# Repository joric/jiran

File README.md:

# Jiran Keyboard

Jiran keyboard - is a ergo split keyboard.

This is archived copy. Actual version is at https://github.com/Ladniy/jiran-keyboard

## Downloads

* [TheCoolerJiran_Gerbers.zip](https://github.com/joric/jiran/raw/master/Jiran/Gerbers/TheCoolerJiran_Gerbers.zip)

## Pictures

## References

* https://github.com/Ladniy/Jiran

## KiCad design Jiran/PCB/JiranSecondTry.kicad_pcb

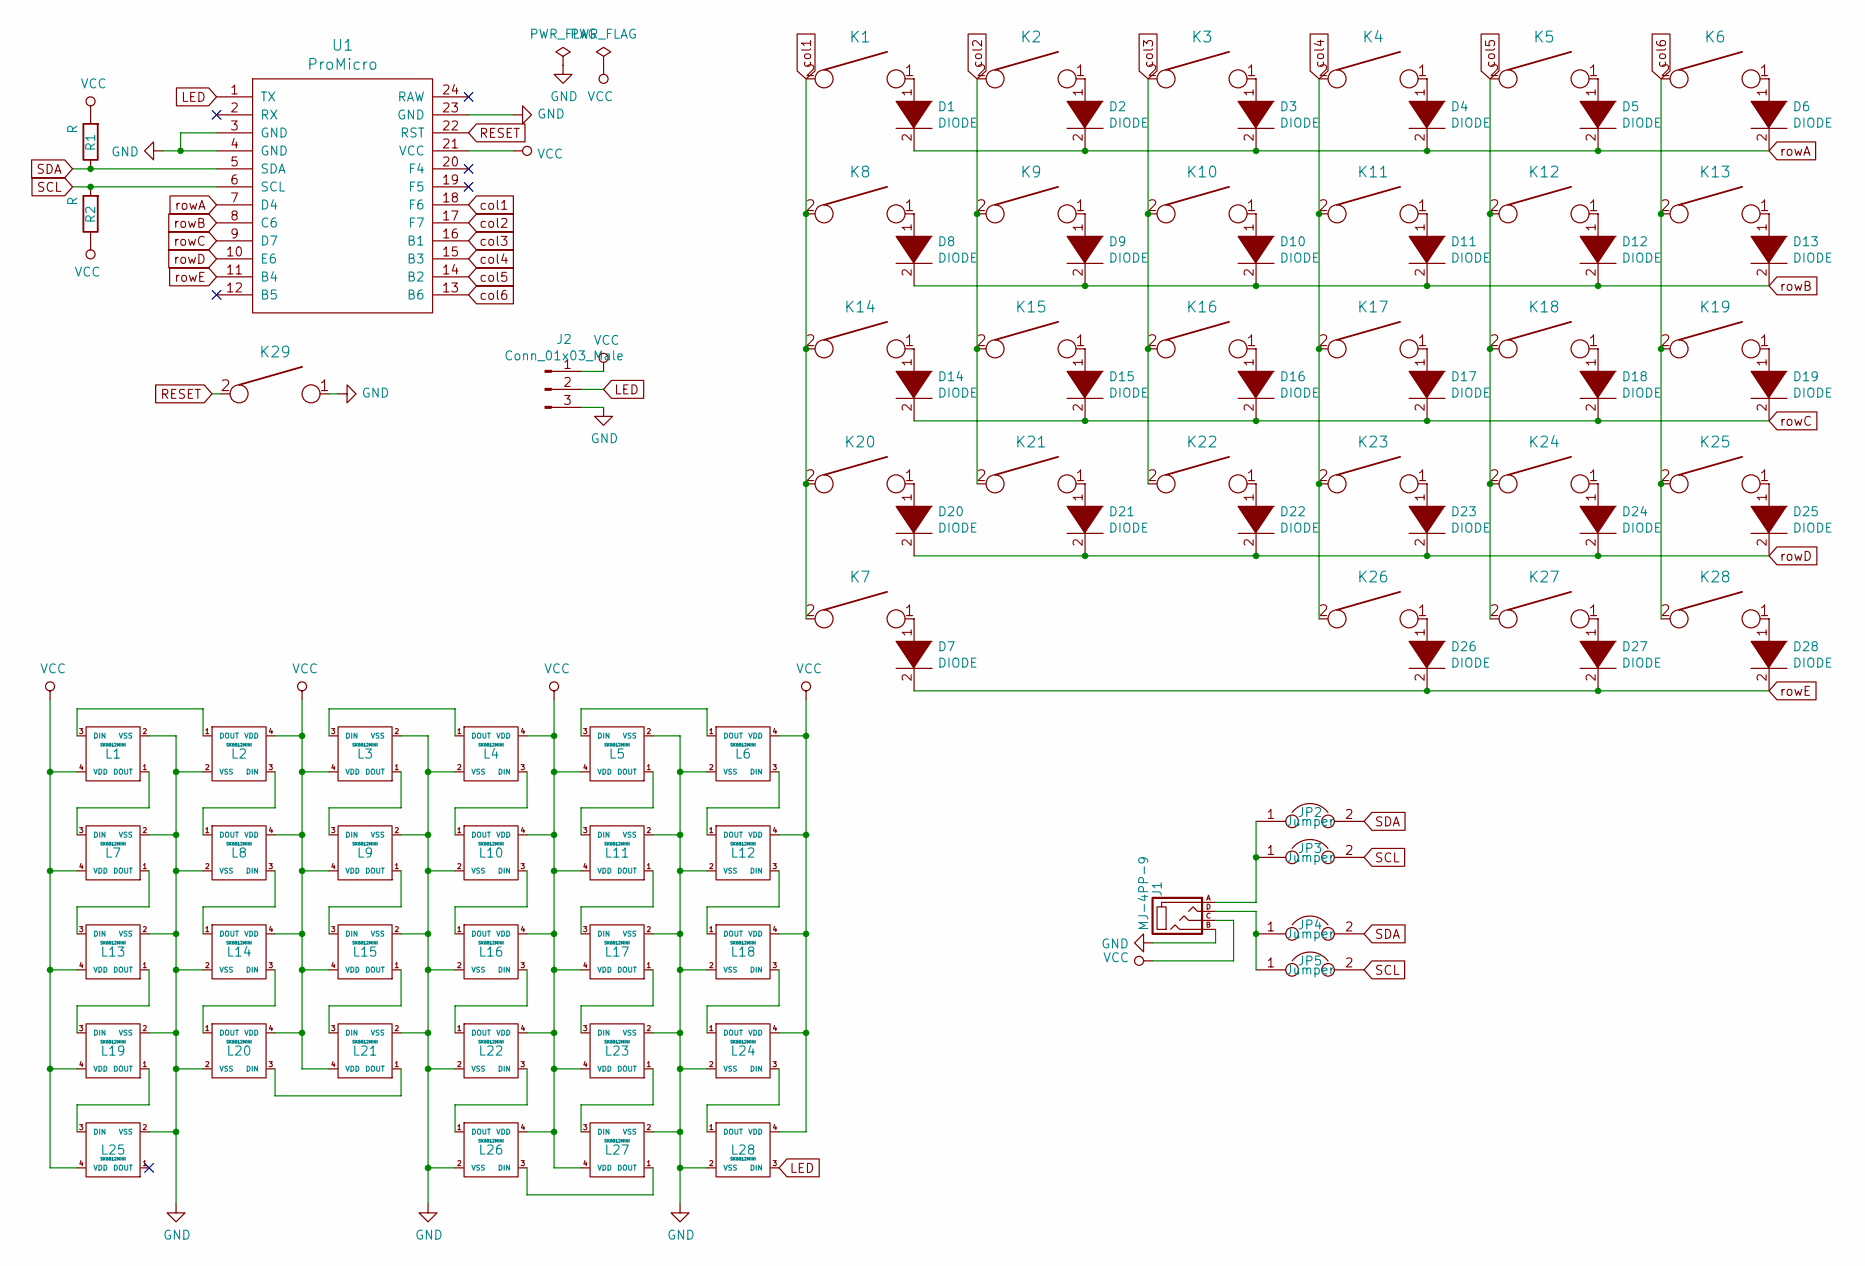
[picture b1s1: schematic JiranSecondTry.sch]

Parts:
D1, D2, D3, D4, D5, D6, D7, D8, D9, D10, D11, D12, D13, D14, D15, D16, D17, D18, D19, D20, D21, D22, D23, D24, D25, D26, D27, D28: DIODE; Diode-dual
J1: MJ-4PP-9; MJ-4PP-9_Dual
J2: Conn_01x03_Male; 3_Pin_Jumper
JP2, JP3, JP4, JP5: Jumper
K1, K2, K3, K4, K5, K6, K7, K8, K9, K10, K11, K12, K13, K14, K15, K16, K17, K18, K19, K20, K21, K22, K23, K24, K25, K26, K27, K28: KEYSW; MX_ALPS_PG1350_noLed
K29: KEYSW; ResetSW
L1, L2, L3, L4, L5, L6, L7, L8, L9, L10, L11, L12, L13, L14, L15, L16, L17, L18, L19, L20, L21, L22, L23, L24, L25, L26, L27, L28: SK6812MINI; SK6812MINI_rev
R1, R2: R; Resistor-Hybrid
U1: ProMicro; ProMicro_v2_1side

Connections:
GND: J1.B, J2.3, K29.1, L1.2 (VSS), L2.2 (VSS), L3.2 (VSS), L4.2 (VSS), L5.2 (VSS), L6.2 (VSS), L7.2 (VSS), L8.2 (VSS), L9.2 (VSS), L10.2 (VSS), L11.2 (VSS), L12.2 (VSS), L13.2 (VSS), L14.2 (VSS), L15.2 (VSS), L16.2 (VSS), L17.2 (VSS), L18.2 (VSS), L19.2 (VSS), L20.2 (VSS), L21.2 (VSS), L22.2 (VSS), L23.2 (VSS), L24.2 (VSS), L25.2 (VSS), L26.2 (VSS), L27.2 (VSS), L28.2 (VSS), U1.3 (GND), U1.4 (GND), U1.23 (GND)
LED: J2.2, L28.3 (DIN), U1.1 (TX)
unnamed: D1.1 (K), K1.1
unnamed: D2.1 (K), K2.1
unnamed: D3.1 (K), K3.1
unnamed: D4.1 (K), K4.1
unnamed: D5.1 (K), K5.1
unnamed: D6.1 (K), K6.1
unnamed: D7.1 (K), K7.1
unnamed: D8.1 (K), K8.1
unnamed: D9.1 (K), K9.1
unnamed: D10.1 (K), K10.1
unnamed: D11.1 (K), K11.1
unnamed: D12.1 (K), K12.1
unnamed: D13.1 (K), K13.1
unnamed: D14.1 (K), K14.1
unnamed: D15.1 (K), K15.1
unnamed: D16.1 (K), K16.1
unnamed: D17.1 (K), K17.1
unnamed: D18.1 (K), K18.1
unnamed: D19.1 (K), K19.1
unnamed: D20.1 (K), K20.1
unnamed: D21.1 (K), K21.1
unnamed: D22.1 (K), K22.1
unnamed: D23.1 (K), K23.1
unnamed: D24.1 (K), K24.1
unnamed: D25.1 (K), K25.1
unnamed: D26.1 (K), K26.1
unnamed: D27.1 (K), K27.1
unnamed: D28.1 (K), K28.1
unnamed: J1.A, JP2.1, JP3.1
unnamed: J1.D, JP4.1, JP5.1
unnamed: L1.1 (DOUT), L7.3 (DIN)
unnamed: L1.3 (DIN), L2.1 (DOUT)
unnamed: L2.3 (DIN), L8.1 (DOUT)
unnamed: L3.1 (DOUT), L9.3 (DIN)
unnamed: L3.3 (DIN), L4.1 (DOUT)
unnamed: L5.3 (DIN), L6.1 (DOUT)
unnamed: L4.3 (DIN), L10.1 (DOUT)
unnamed: L10.3 (DIN), L16.1 (DOUT)
unnamed: L11.1 (DOUT), L17.3 (DIN)
unnamed: L5.1 (DOUT), L11.3 (DIN)
unnamed: L6.3 (DIN), L12.1 (DOUT)
unnamed: L12.3 (DIN), L18.1 (DOUT)
unnamed: L13.1 (DOUT), L19.3 (DIN)
unnamed: L7.1 (DOUT), L13.3 (DIN)
unnamed: L8.3 (DIN), L14.1 (DOUT)
unnamed: L14.3 (DIN), L20.1 (DOUT)
unnamed: L15.1 (DOUT), L21.3 (DIN)
unnamed: L9.1 (DOUT), L15.3 (DIN)
unnamed: L16.3 (DIN), L22.1 (DOUT)
unnamed: L17.1 (DOUT), L23.3 (DIN)
unnamed: L18.3 (DIN), L24.1 (DOUT)
unnamed: L19.1 (DOUT), L25.3 (DIN)
unnamed: L20.3 (DIN), L21.1 (DOUT)
unnamed: L22.3 (DIN), L26.1 (DOUT)
unnamed: L23.1 (DOUT), L27.3 (DIN)
unnamed: L24.3 (DIN), L28.1 (DOUT)
unnamed: L26.3 (DIN), L27.1 (DOUT)
RESET: K29.2, U1.22 (RST)
SCL: JP3.2, JP5.2, R2.2, U1.6 (SCL)
SDA: JP2.2, JP4.2, R1.1, U1.5 (SDA)
VCC: J1.C, J2.1, L1.4 (VDD), L2.4 (VDD), L3.4 (VDD), L4.4 (VDD), L5.4 (VDD), L6.4 (VDD), L7.4 (VDD), L8.4 (VDD), L9.4 (VDD), L10.4 (VDD), L11.4 (VDD), L12.4 (VDD), L13.4 (VDD), L14.4 (VDD), L15.4 (VDD), L16.4 (VDD), L17.4 (VDD), L18.4 (VDD), L19.4 (VDD), L20.4 (VDD), L21.4 (VDD), L22.4 (VDD), L23.4 (VDD), L24.4 (VDD), L25.4 (VDD), L26.4 (VDD), L27.4 (VDD), L28.4 (VDD), R1.2, R2.1, U1.21 (VCC)
col1: K1.2, K7.2, K8.2, K14.2, K20.2, U1.18 (F6)
col2: K2.2, K9.2, K15.2, K21.2, U1.17 (F7)
col3: K3.2, K10.2, K16.2, K22.2, U1.16 (B1)
col4: K4.2, K11.2, K17.2, K23.2, K26.2, U1.15 (B3)
col5: K5.2, K12.2, K18.2, K24.2, K27.2, U1.14 (B2)
col6: K6.2, K13.2, K19.2, K25.2, K28.2, U1.13 (B6)
rowA: D1.2 (A), D2.2 (A), D3.2 (A), D4.2 (A), D5.2 (A), D6.2 (A), U1.7 (D4)
rowB: D8.2 (A), D9.2 (A), D10.2 (A), D11.2 (A), D12.2 (A), D13.2 (A), U1.8 (C6)
rowC: D14.2 (A), D15.2 (A), D16.2 (A), D17.2 (A), D18.2 (A), D19.2 (A), U1.9 (D7)
rowD: D20.2 (A), D21.2 (A), D22.2 (A), D23.2 (A), D24.2 (A), D25.2 (A), U1.10 (E6)
rowE: D7.2 (A), D26.2 (A), D27.2 (A), D28.2 (A), U1.11 (B4)

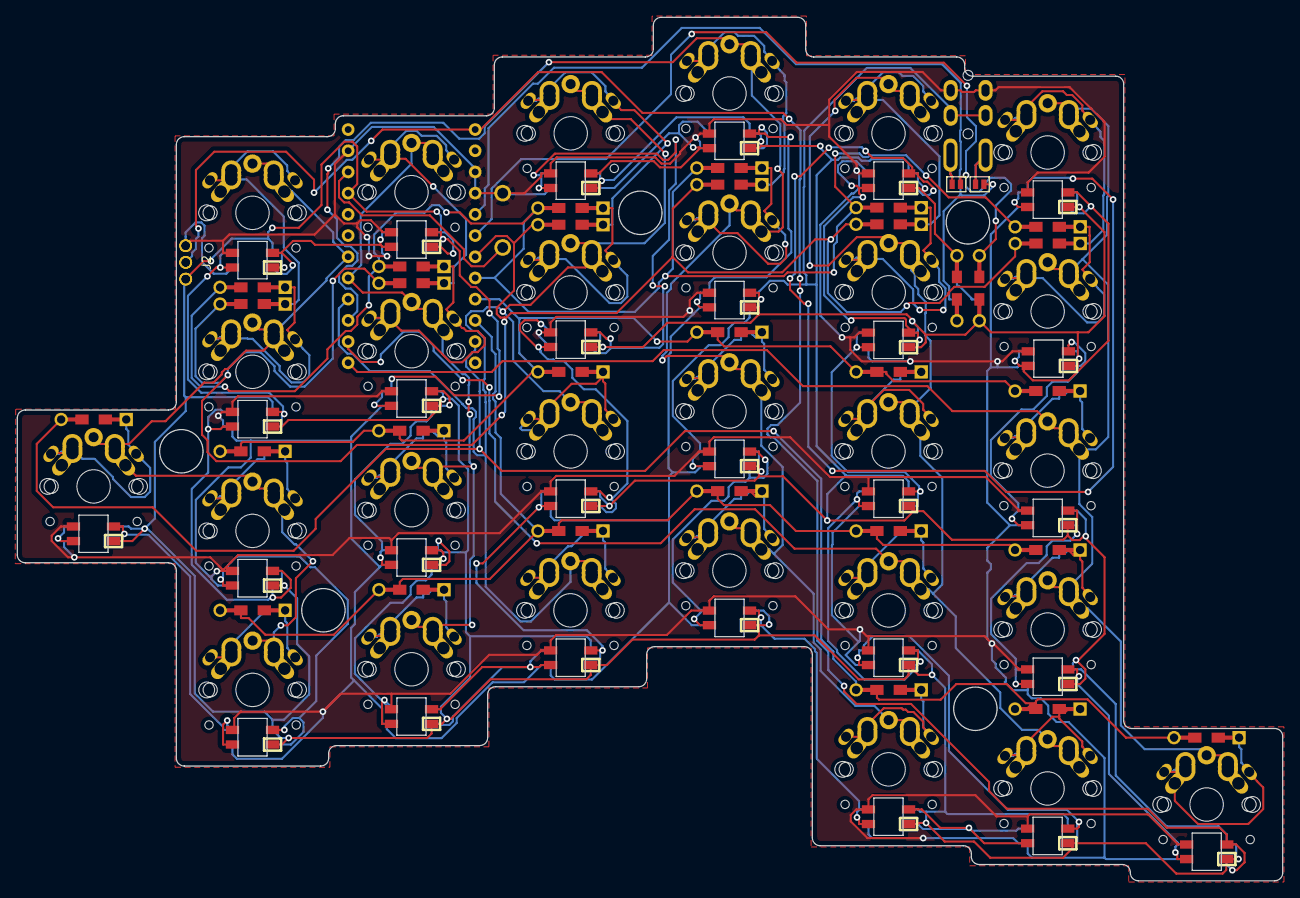
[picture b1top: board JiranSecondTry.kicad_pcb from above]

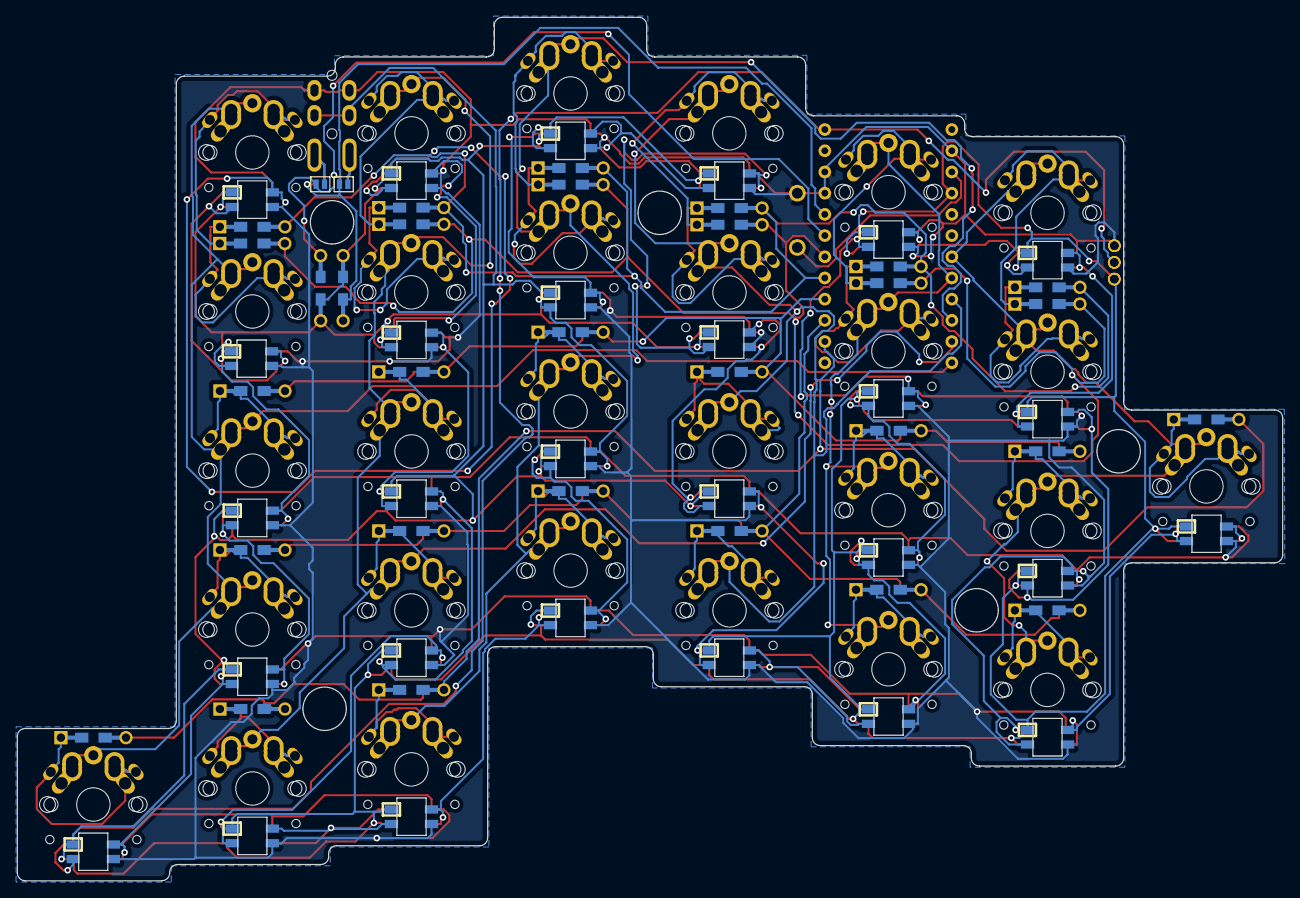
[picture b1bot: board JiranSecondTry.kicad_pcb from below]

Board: 2 copper layers, 151.6 x 103.4 mm, 94 parts (2 on the bottom side), 74 nets.

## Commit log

2019-04-15 Finished files
2020-06-13 updated files
